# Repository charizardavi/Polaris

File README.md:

# Polaris Flight Computer

System clock: 480mhz

Interfaces:
- ST-Link
- USB OTG (type C)
- 5x Servo/BLDC Motor output

currently using:
- STM32H743ZIT6 MCU
- LSM6DSO 6-axis IMU
- BMP388 barometer
- SDMMC interface on MCU to write to micro SD card

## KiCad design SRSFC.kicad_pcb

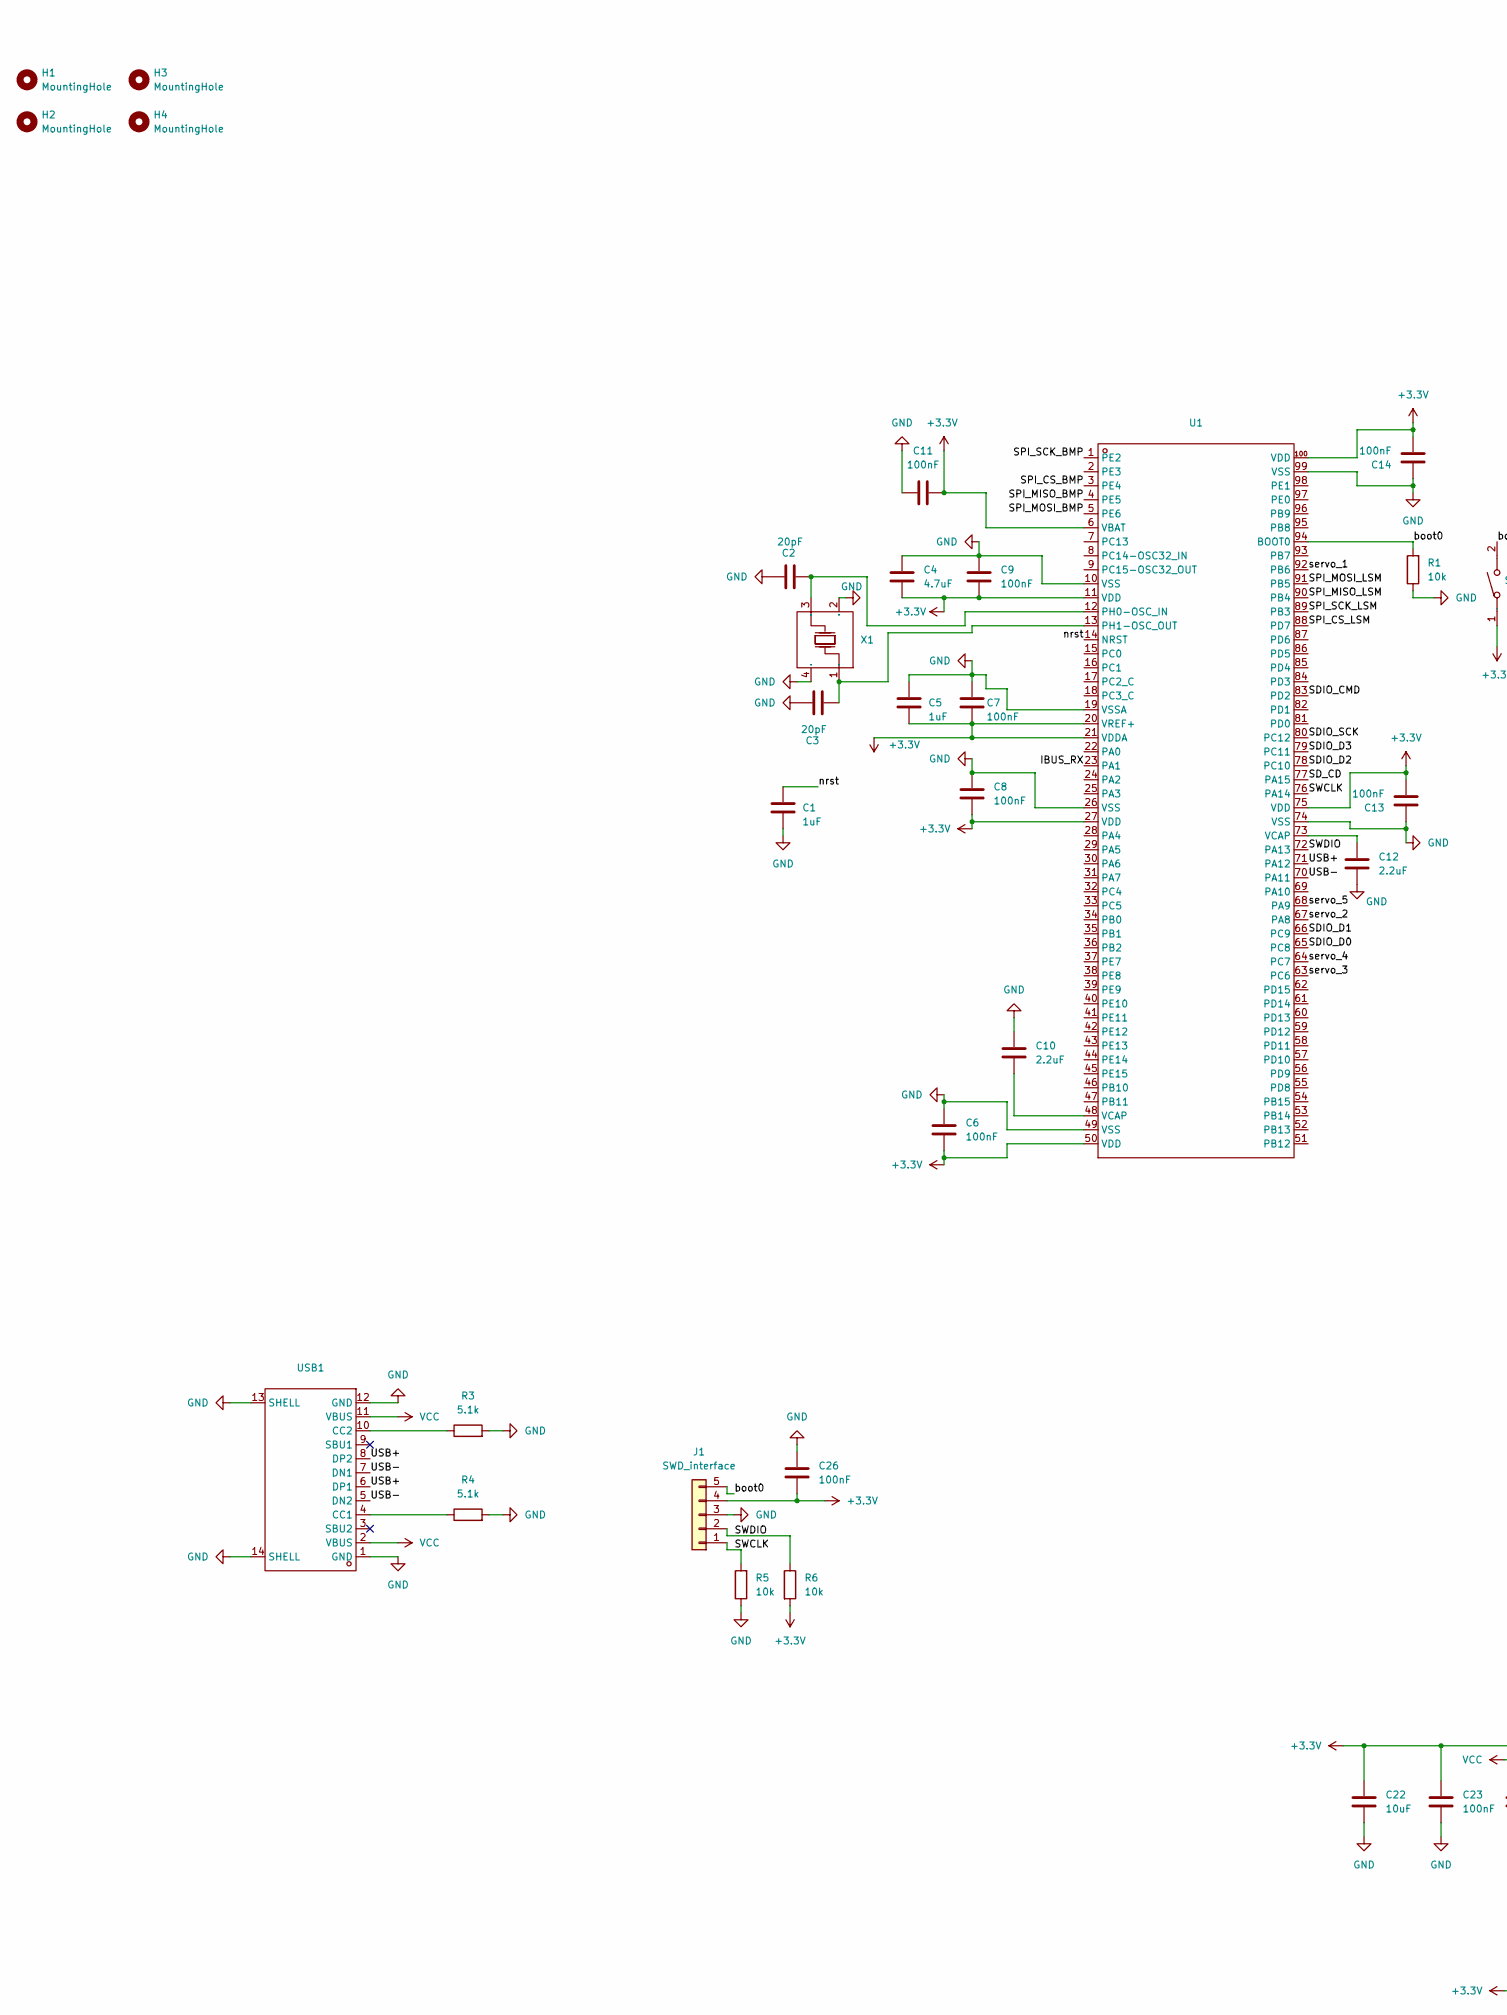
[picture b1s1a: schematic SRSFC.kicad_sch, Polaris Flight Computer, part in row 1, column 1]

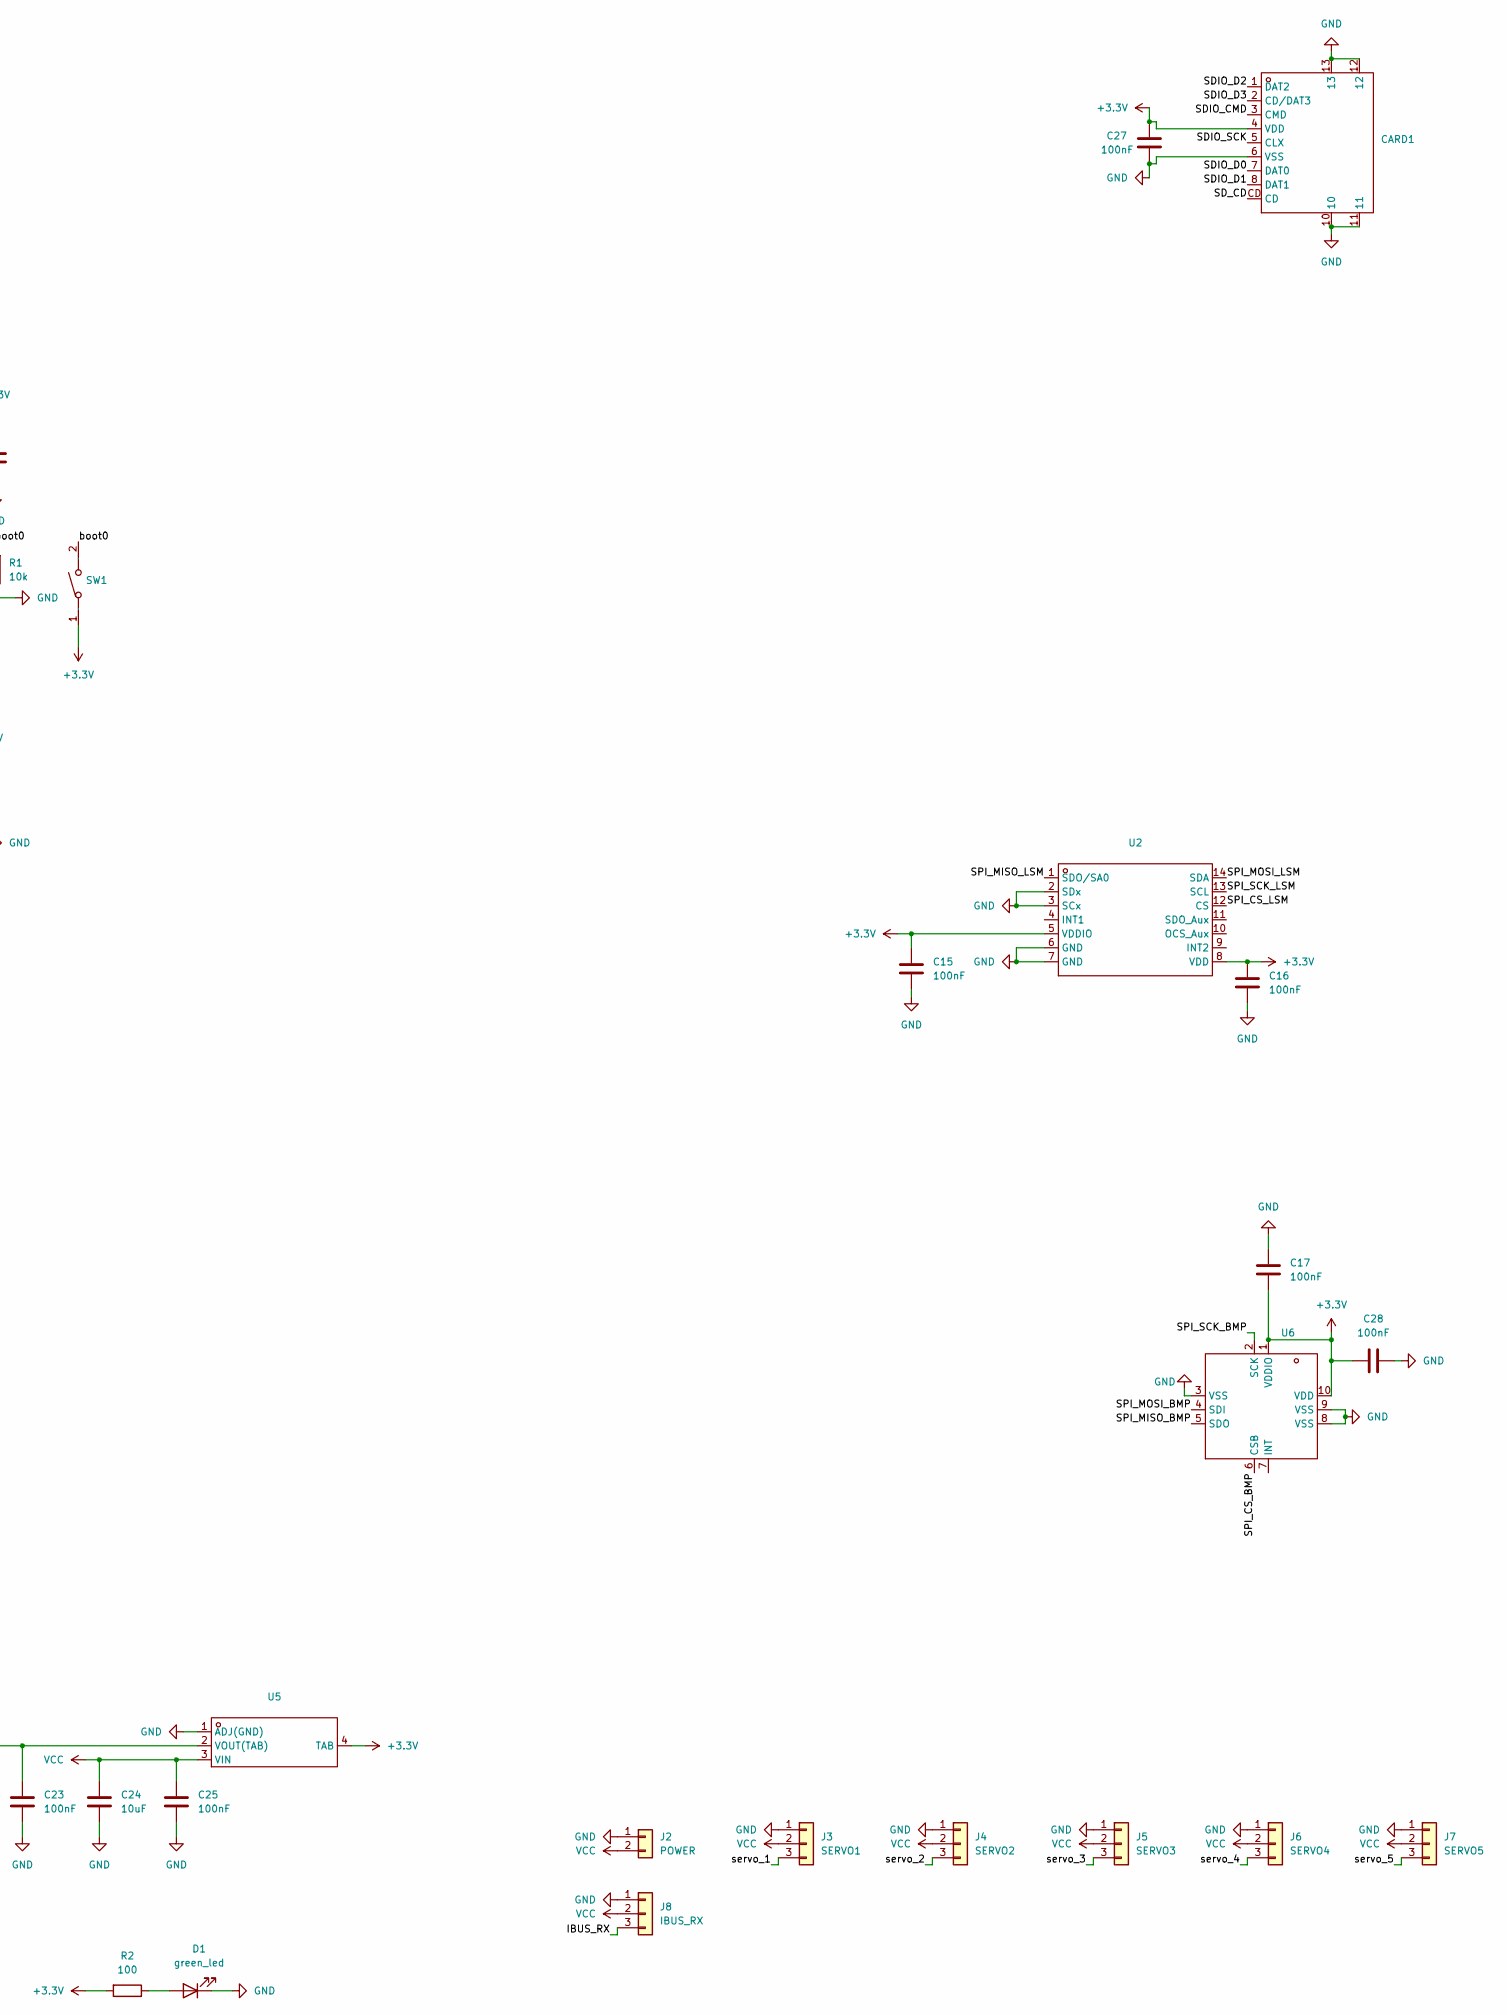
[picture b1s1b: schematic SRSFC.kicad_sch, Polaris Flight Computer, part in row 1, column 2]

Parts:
C1, C5: 1uF; C_0402_1005Metric
C2, C3: 20pF; C_0402_1005Metric
C4: 4.7uF; C_0402_1005Metric
C6, C7, C8, C9, C11, C13, C14, C15, C16, C17, C23, C25, C26, C27, C28: 100nF; C_0402_1005Metric
C10, C12: 2.2uF; C_0402_1005Metric
C22, C24: 10uF; C_0402_1005Metric
CARD1: TF-SMD_TF-PUSH; Manufacturer Part TF PUSH; LCSC Part Name 自弹式 MicroSD卡(TF卡) 卡座
D1: green_led; LED_0603_1608Metric
H1, H2, H3, H4: MountingHole; MountingHole_4.3mm_M4_DIN965_Pad
J1: SWD_interface; PinHeader_1x05_P2.54mm_Vertical
J2: POWER; PinHeader_1x02_P2.54mm_Vertical
J3: SERVO1; PinHeader_1x03_P2.54mm_Vertical
J4: SERVO2; PinHeader_1x03_P2.54mm_Vertical
J5: SERVO3; PinHeader_1x03_P2.54mm_Vertical
J6: SERVO4; PinHeader_1x03_P2.54mm_Vertical
J7: SERVO5; PinHeader_1x03_P2.54mm_Vertical
J8: IBUS_RX; PinHeader_1x03_P2.54mm_Vertical
R1, R5, R6: 10k; R_0402_1005Metric
R2: 100; R_0402_1005Metric
R3, R4: 5.1k; R_0402_1005Metric
SW1: SW-SMD_L3.9-W3.0-P4.45; Manufacturer Part TS-1088-AR02016; LCSC Part Name 4*3*2mm 立贴 轻触开关
U1: QFP-100_L14.0-W14.0-P0.50-LS16.0-BL; Manufacturer Part STM32H750VBT6TR; LCSC Part Name 带DSP和DP-FPU的高性能ARM Cortex-M7 MCU，具有128 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
U2: LGA-14L_L3.0-W2.5-P0.50-TL; Manufacturer Part LSM6DSOWTR; LCSC Part Name LSM6DSOWTR
U5: SOT-223-4_L6.5-W3.5-P2.30-LS7.0-BR; Manufacturer Part AMS1117-3.3; LCSC Part Name 输出:3.3V 电流:1A 耐压:12V
U6: SENSORM-SMD_BMP388; Manufacturer Part BMP388; LCSC Part Name BMP388
USB1: USB-C-SMD_TYPE-C-6PIN-2MD-073; Manufacturer Part TYPE-C 16PIN 2MD(073); LCSC Part Name Type-C 母 卧贴
X1: 25MHz; OSC-SMD_4P-L3.2-W2.5-BL; Manufacturer Part X322525MSB4SI; LCSC Part Name 25MHz ±10ppm 20pF

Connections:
+3.3V: C4.2, C5.1, C6.1, C7.1, C8.1, C9.1, C11.2, C13.1, C14.1, C15.1, C16.2, C17.1, C22.1, C23.1, C26.1, C27.2, C28.1, CARD1.4 (VDD), J1.4, R2.2, R6.2, SW1.1, U1.6 (VBAT), U1.11 (VDD), U1.20 (VREF+), U1.21 (VDDA), U1.27 (VDD), U1.50 (VDD), U1.75 (VDD), U1.100 (VDD), U2.5 (VDDIO), U2.8 (VDD), U5.2 (VOUT(TAB)), U5.4 (TAB), U6.1 (VDDIO), U6.10 (VDD)
/IBUS_RX: J8.3, U1.23 (PA1)
/SDIO_CMD: CARD1.3 (CMD), U1.83 (PD2)
/SDIO_D0: CARD1.7 (DAT0), U1.65 (PC8)
/SDIO_D1: CARD1.8 (DAT1), U1.66 (PC9)
/SDIO_D2: CARD1.1 (DAT2), U1.78 (PC10)
/SDIO_D3: CARD1.2 (CD/DAT3), U1.79 (PC11)
/SDIO_SCK: CARD1.5 (CLX), U1.80 (PC12)
/SD_CD: CARD1.CD, U1.77 (PA15)
/SPI_CS_BMP: U1.3 (PE4), U6.6 (CSB)
/SPI_CS_LSM: U1.88 (PD7), U2.12 (CS)
/SPI_MISO_BMP: U1.4 (PE5), U6.5 (SDO)
/SPI_MISO_LSM: U1.90 (PB4), U2.1 (SDO/SA0)
/SPI_MOSI_BMP: U1.5 (PE6), U6.4 (SDI)
/SPI_MOSI_LSM: U1.91 (PB5), U2.14 (SDA)
/SPI_SCK_BMP: U1.1 (PE2), U6.2 (SCK)
/SPI_SCK_LSM: U1.89 (PB3), U2.13 (SCL)
/SWCLK: J1.1, R5.2, U1.76 (PA14)
/SWDIO: J1.2, R6.1, U1.72 (PA13)
/USB+: U1.71 (PA12), USB1.6 (DP1), USB1.8 (DP2)
/USB-: U1.70 (PA11), USB1.5 (DN2), USB1.7 (DN1)
/boot0: J1.5, R1.2, SW1.2, U1.94 (BOOT0)
/nrst: C1.2, U1.14 (NRST)
/servo_1: J3.3, U1.92 (PB6)
/servo_2: J4.3, U1.67 (PA8)
/servo_3: J5.3, U1.63 (PC6)
/servo_4: J6.3, U1.64 (PC7)
/servo_5: J7.3, U1.68 (PA9)
GND: C1.1, C2.2, C3.2, C4.1, C5.2, C6.2, C7.2, C8.2, C9.2, C10.2, C11.1, C12.2, C13.2, C14.2, C15.2, C16.1, C17.2, C22.2, C23.2, C24.2, C25.2, C26.2, C27.1, C28.2, CARD1.6 (VSS), CARD1.10, CARD1.11, CARD1.12, CARD1.13, D1.1 (K), J1.3, J2.1, J3.1, J4.1, J5.1, J6.1, J7.1, J8.1, R1.1, R3.2, R4.2, R5.1, U1.10 (VSS), U1.19 (VSSA), U1.26 (VSS), U1.49 (VSS), U1.74 (VSS), U1.99 (VSS), U2.2 (SDx), U2.3 (SCx), U2.6 (GND), U2.7 (GND), U5.1 (ADJ(GND)), U6.3 (VSS), U6.8 (VSS), U6.9 (VSS), USB1.1 (GND), USB1.12 (GND), USB1.13 (SHELL), USB1.14 (SHELL), X1.2 (GND), X1.4 (GND)
unnamed: C10.1, U1.48 (VCAP)
unnamed: C12.1, U1.73 (VCAP)
unnamed: D1.2 (A), R2.1
unnamed: C2.1, U1.12 (PH0-OSC_IN), X1.3 (OSC2)
unnamed: C3.1, U1.13 (PH1-OSC_OUT), X1.1 (OSC1)
unnamed: R4.1, USB1.4 (CC1)
unnamed: R3.1, USB1.10 (CC2)
VCC: C24.1, C25.1, J2.2, J3.2, J4.2, J5.2, J6.2, J7.2, J8.2, U5.3 (VIN), USB1.2 (VBUS), USB1.11 (VBUS)

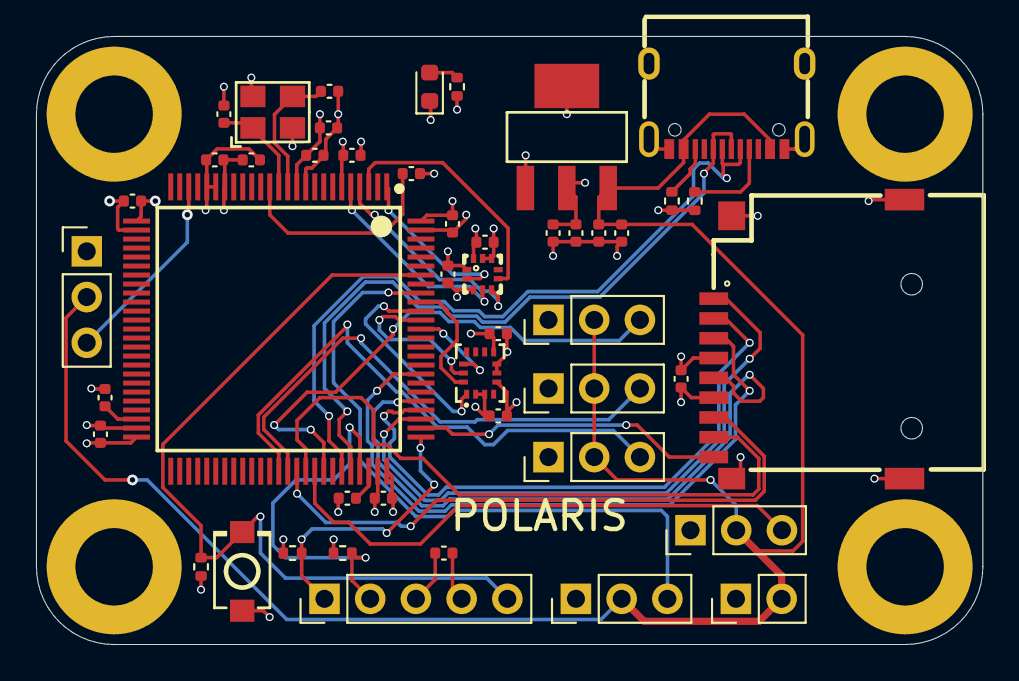
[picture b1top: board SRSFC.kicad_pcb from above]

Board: 4 copper layers, 52.6 x 33.8 mm, 51 parts (0 on the bottom side), 37 nets.

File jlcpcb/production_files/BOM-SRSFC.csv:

Comment,Designator,Footprint,LCSC
20pF,"C2,C3",C_0402_1005Metric,C107000
~,U1,QFP-100_L14.0-W14.0-P0.50-LS16.0-BL,C114409
25MHz,X1,OSC-SMD_4P-L3.2-W2.5-BL,C13740
1uF,"C1,C5",C_0402_1005Metric,C14445
2.2uF,"C10,C12",C_0402_1005Metric,C170151
100,R2,R_0402_1005Metric,C25076
10k,"R1,R5,R6",R_0402_1005Metric,C25744
5.1k,"R3,R4",R_0402_1005Metric,C25905
~,USB1,USB-C-SMD_TYPE-C-6PIN-2MD-073,C2765186
~,U2,LGA-14L_L3.0-W2.5-P0.50-TL,C2829074
~,U5,SOT-223-4_L6.5-W3.5-P2.30-LS7.0-BR,C347222
4.7uF,C4,C_0402_1005Metric,C368809
~,CARD1,TF-SMD_TF-PUSH,C393941
100nF,"C11,C13,C14,C15,C16,C17,C23,C25,C26,C27,C28,C6,C7,C8,C9",C_0402_1005Metric,C60474
~,SW1,SW-SMD_L3.9-W3.0-P4.45,C720477
10uF,"C22,C24",C_0402_1005Metric,C77000
~,U6,SENSORM-SMD_BMP388,C779278
green_led,D1,LED_0603_1608Metric,C965799

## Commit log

2024-11-10 added BMP388
2024-11-11 added readme
2024-11-11 fixed some schema layout
2024-11-12 added servo connectors, schema done (probably)
2024-11-22 finished v1 (bad) layout)
2024-11-22 good layout done, DRC passes
2024-11-26 swapped ICM-20948 for LSM6DSO, added more TIM outputs
2024-11-26 added silkscreen, added UART interface
2024-11-27 changed sensors from i2c to SPI, fixed silkscreen
2024-11-30 final commit before ordering
2024-12-08 fixed readme
2024-12-08 added image preview
2024-12-08 fixed image preview
